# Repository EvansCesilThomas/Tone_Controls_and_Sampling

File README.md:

3-in-1 (Overdrive, Distortion, Fuzz) effects for guitar (PCB is WIP)
Proposed realtime audio sampling and pitch-sihting for a synthesizer functionality (WIP)

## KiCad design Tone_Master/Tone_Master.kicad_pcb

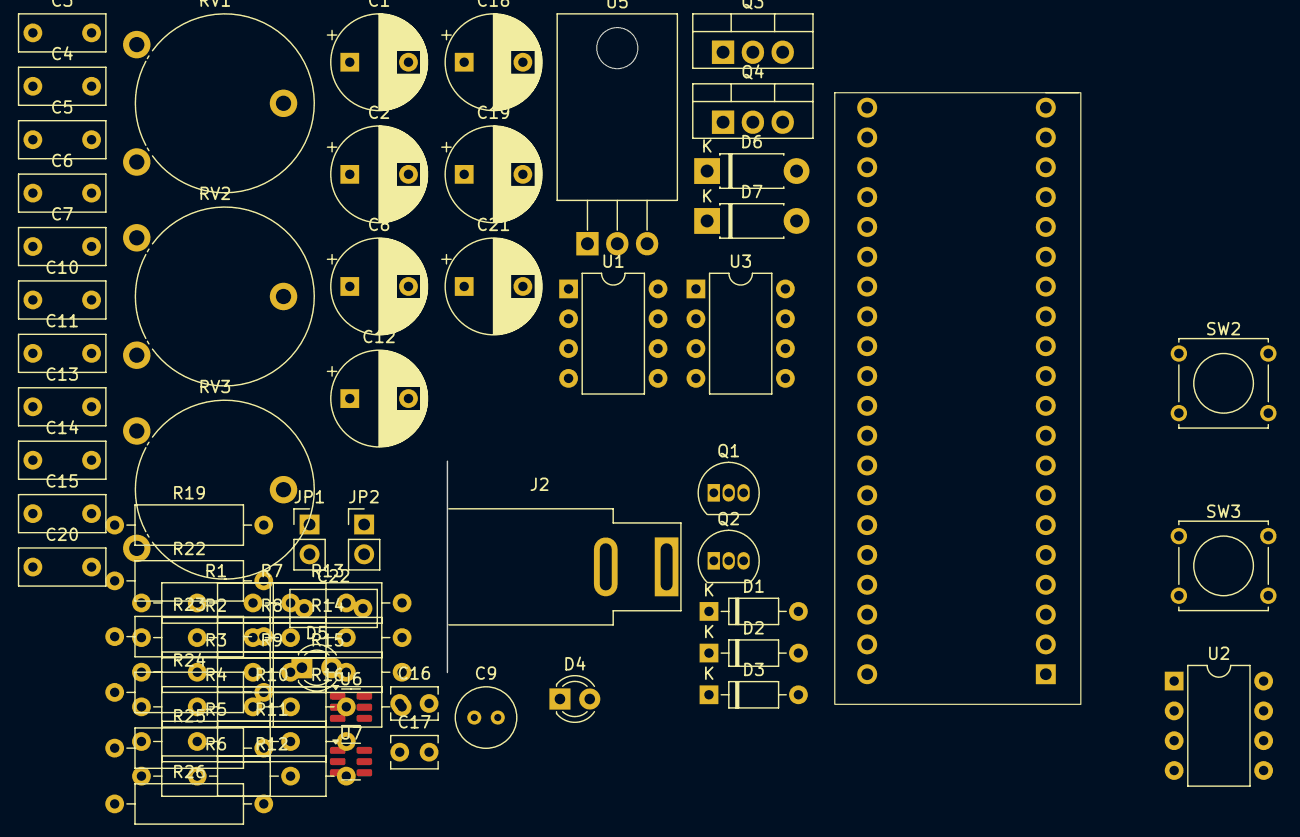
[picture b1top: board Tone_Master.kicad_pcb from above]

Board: 2 copper layers, 70 parts (0 on the bottom side), 44 nets, no tracks yet.

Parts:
C1, C2, C21: 47uF; CP_Radial_D8.0mm_P5.00mm
C3, C4, C11, C20: 470nF; C_Rect_L7.2mm_W3.0mm_P5.00mm_FKS2_FKP2_MKS2_MKP2
C5: 22nF; C_Rect_L7.2mm_W3.0mm_P5.00mm_FKS2_FKP2_MKS2_MKP2
C6: 10nF; C_Rect_L7.2mm_W3.0mm_P5.00mm_FKS2_FKP2_MKS2_MKP2
C7: 50pF; C_Rect_L7.2mm_W3.0mm_P5.00mm_FKS2_FKP2_MKS2_MKP2
C8, C18: 1uF; CP_Radial_D8.0mm_P5.00mm
C9: 50pF; C_Radial_D5.0mm_H7.0mm_P2.00mm
C10: 1uF; C_Rect_L7.2mm_W3.0mm_P5.00mm_FKS2_FKP2_MKS2_MKP2
C12: 22uF; CP_Radial_D8.0mm_P5.00mm
C13, C14, C22: 47nF; C_Rect_L7.2mm_W3.0mm_P5.00mm_FKS2_FKP2_MKS2_MKP2
C15: 100pF; C_Rect_L7.2mm_W3.0mm_P5.00mm_FKS2_FKP2_MKS2_MKP2
C16, C17: 10nF; C_Disc_D3.8mm_W2.6mm_P2.50mm
C19: 1000uF; CP_Radial_D8.0mm_P5.00mm
D1, D2, D3: 1N4148; D_DO-35_SOD27_P7.62mm_Horizontal
D4, D5: LED; LED_D3.0mm_Clear
D6: 3.3V; D_DO-41_SOD81_P7.62mm_Horizontal
D7: 1N4007; D_DO-41_SOD81_P7.62mm_Horizontal
J2: Barrel_Jack; BarrelJack_SwitchcraftConxall_RAPC10U_Horizontal
JP1: Source Select; PinHeader_1x02_P2.54mm_Vertical
JP2: Tone Control Select; PinHeader_1x02_P2.54mm_Vertical
Q1, Q2: 2N3904; TO-92_Inline
Q3: TIP41C; TO-220-3_Vertical
Q4: TIP42C; TO-220-3_Vertical
R1, R2, R22: 47k; R_Axial_DIN0309_L9.0mm_D3.2mm_P12.70mm_Horizontal
R3, R4, R19, R24: 1Meg; R_Axial_DIN0309_L9.0mm_D3.2mm_P12.70mm_Horizontal
R5, R6: 10K; R_Axial_DIN0309_L9.0mm_D3.2mm_P12.70mm_Horizontal
R7: 330; R_Axial_DIN0309_L9.0mm_D3.2mm_P12.70mm_Horizontal
R8: 5.6k; R_Axial_DIN0309_L9.0mm_D3.2mm_P12.70mm_Horizontal
R9, R25: 10k; R_Axial_DIN0309_L9.0mm_D3.2mm_P12.70mm_Horizontal
R10: 100k; R_Axial_DIN0309_L9.0mm_D3.2mm_P12.70mm_Horizontal
R11: 680; R_Axial_DIN0309_L9.0mm_D3.2mm_P12.70mm_Horizontal
R12: 4.7K; R_Axial_DIN0309_L9.0mm_D3.2mm_P12.70mm_Horizontal
R13: 1K; R_Axial_DIN0309_L9.0mm_D3.2mm_P12.70mm_Horizontal
R14: 330K; R_Axial_DIN0309_L9.0mm_D3.2mm_P12.70mm_Horizontal
R15, R16: 22K; R_Axial_DIN0309_L9.0mm_D3.2mm_P12.70mm_Horizontal
R23: 3K; R_Axial_DIN0309_L9.0mm_D3.2mm_P12.70mm_Horizontal
R26: 22k; R_Axial_DIN0309_L9.0mm_D3.2mm_P12.70mm_Horizontal
RV1: 100k; Potentiometer_Piher_PT-15-V02_Vertical
RV2: 100K; Potentiometer_Piher_PT-15-V02_Vertical
RV3: 500K; Potentiometer_Piher_PT-15-V02_Vertical
SW2: DSP_EN; SW_Tactile_Straight_KSA0Axx1LFTR
SW3: Chorus_EN; SW_Tactile_Straight_KSA0Axx1LFTR
U1, U2, U3: TL072; DIP-8_W7.62mm
U4: Arduino_Nano
U5: LM7805_TO220; TO-220-3_Horizontal_TabDown
U6, U7: MCP4725xxx-xCH; SOT-23-6

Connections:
+9V: C2.1, Q3.2 (C), R2.2, R7.2, R9.2, R22.1, U1.8 (V+), U2.8 (V+), U3.8 (V+), U5.1 (VI)
/3V3: U4.48 (3V3), U7.5 (VDD)
/4.5V_ref: C1.1, R1.2, R2.1, R3.2, R4.2, R19.2, U2.5 (+)
/5V: U4.5V, U5.3 (VO), U6.3 (VDD)
/Distortion_OUT: C13.1, D4.2 (A), D5.1 (K), R11.1
DSP: SW2.2, U4.15 (A5)
GND: C1.2, C2.2, C7.2, C12.2, C13.2, C14.1, C17.1, C21.2, C22.2, D4.1 (K), D5.2 (A), D7.1 (K), J2.2, Q2.1 (E), Q4.2 (C), R1.1, R15.1, R23.2, RV3.3, SW2.1, SW3.1, U1.4 (V-), U2.4 (V-), U3.4 (V-), U4.47 (GND), U5.2 (GND), U6.2 (VSS), U7.6 (GND)
unnamed: C3.1, R5.2
unnamed: C5.1, C7.1, R6.1
unnamed: C6.1, R7.1, R8.2
unnamed: C9.2, RV1.2
unnamed: C10.1, R11.2
unnamed: C10.2, C15.1, R14.1, U2.7
unnamed: C11.1, R12.2
unnamed: C14.2, R13.1
unnamed: C16.1, R15.2, RV2.1
unnamed: C17.2, R16.1, RV2.3
unnamed: C18.2, RV3.2
unnamed: C21.1, R22.2, R23.1, R24.2
unnamed: C22.1, R25.2
unnamed: C4.1, D1.2 (A), D3.1 (K), U1.1
unnamed: C9.1, D1.1 (K), D2.2 (A), Q1.1 (E), R10.1, R13.2, RV1.1, U1.2 (-), U2.2 (-)
unnamed: D2.1 (K), D3.2 (A)
unnamed: D6.2 (A), D7.2 (A)
unnamed: JP2.1 (A), RV2.2, RV3.1
unnamed: C16.2, R16.2
unnamed: Q1.2 (B), Q2.3 (C), R9.1
unnamed: Q1.3 (C), R8.1
unnamed: C8.1, Q2.2 (B), R10.2
unnamed: Q3.1 (B), Q4.1 (B), U3.1
unnamed: C19.1, Q3.3 (E), Q4.3 (E), U3.2 (-)
unnamed: C3.2, R3.1, U1.3 (+)
unnamed: C20.2, R24.1, U1.5 (+)
unnamed: R25.1, R26.1, U1.6 (-)
unnamed: C5.2, R4.1, U2.3 (+)
unnamed: C15.2, R12.1, R14.2, U2.6 (-)
unnamed: C18.1, R19.1, U3.3 (+)
PICKUP_OUT: C20.1, J2.1
Preamp_OUT: C8.2, D6.1 (K), R5.1, R6.2, R26.2, U1.7
SCK: U4.13 (A3), U7.3 (SCK)
SCL: U4.42 (B6), U6.5 (SCL)
SDA: U4.43 (B7), U6.4 (SDA)
STM OUT: JP1.1 (A), U6.1 (VOUT)
SW_Effect: SW3.2, U4.16 (A6)

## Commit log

2025-01-20 add block diagram
2025-01-20 add BOM
2025-01-21 Todo: input buffer
2025-01-28 full schematic v1
2025-01-30 Add voltage protection
2025-03-24 Final
2025-03-27 V1.0
2025-10-22 Replace pdf with project circuit version
